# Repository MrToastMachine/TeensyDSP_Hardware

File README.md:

# TeensyDSP Hardware files
Kicad project of files for hardware to use in conjuction with TeensyDSP Firwmware git repo

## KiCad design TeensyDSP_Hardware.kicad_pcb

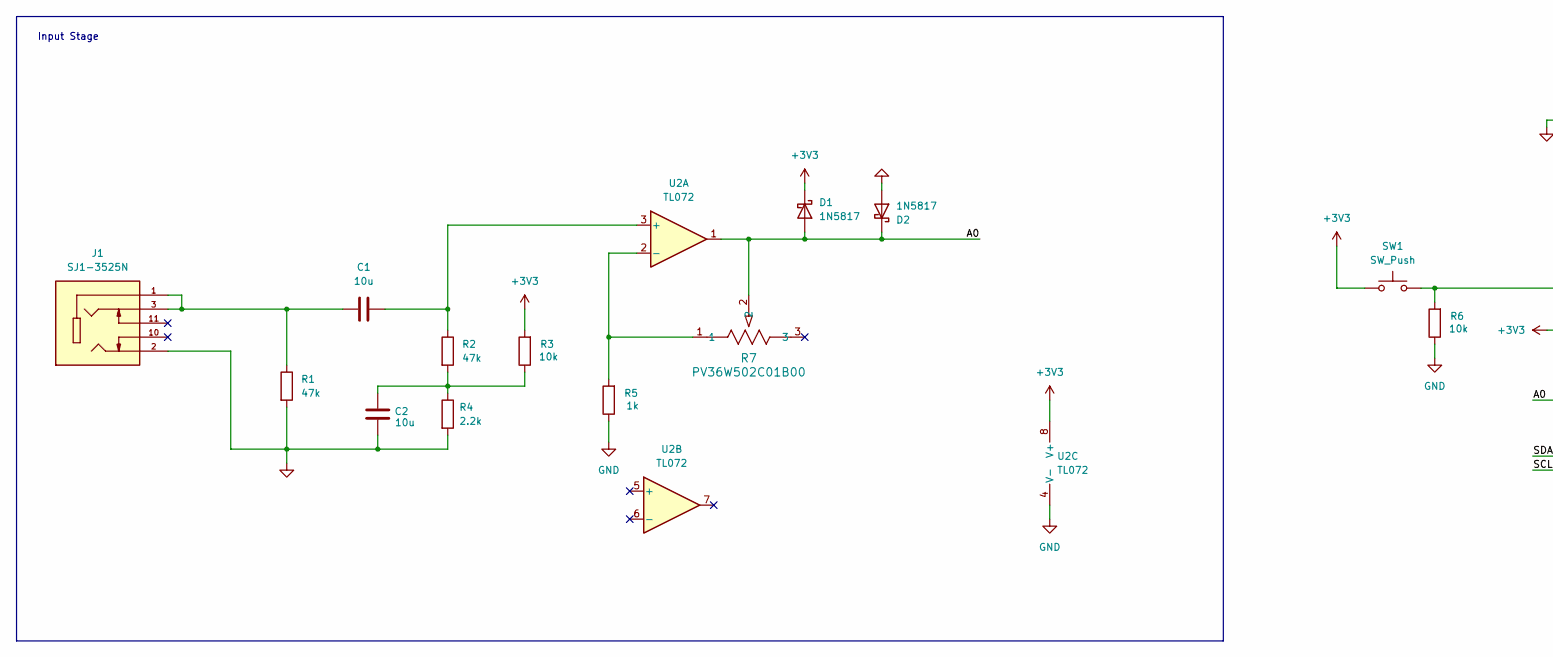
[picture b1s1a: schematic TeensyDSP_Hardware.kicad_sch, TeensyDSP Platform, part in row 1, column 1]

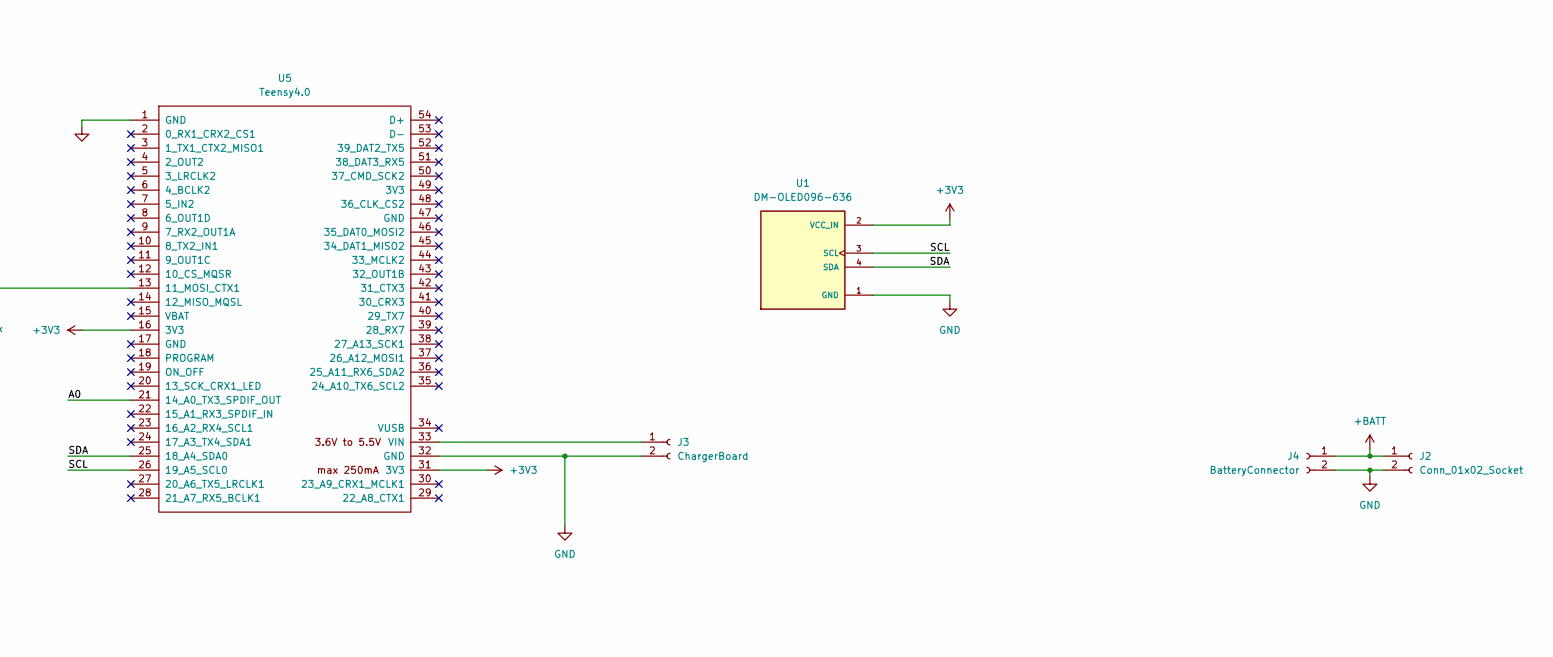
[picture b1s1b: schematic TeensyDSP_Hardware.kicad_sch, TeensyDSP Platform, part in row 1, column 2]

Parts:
C1, C2: 10u; C_Disc_D4.3mm_W1.9mm_P5.00mm
D1, D2: 1N5817; D_DO-41_SOD81_P10.16mm_Horizontal
J1: SJ1-3525N; CUI_SJ1-3525N; PARTREV 1.05
J2: Conn_01x02_Socket; JST_PH_B2B-PH-K_1x02_P2.00mm_Vertical
J3: ChargerBoard; PinHeader_1x02_P2.54mm_Vertical
J4: BatteryConnector; PinHeader_1x02_P2.54mm_Vertical
R1, R2: 47k; R_Axial_DIN0207_L6.3mm_D2.5mm_P7.62mm_Horizontal
R3: 10k; R_Axial_DIN0207_L6.3mm_D2.5mm_P7.62mm_Horizontal
R4: 2.2k; R_Axial_DIN0207_L6.3mm_D2.5mm_P7.62mm_Horizontal
R5: 1k; R_Axial_DIN0207_L6.3mm_D2.5mm_P7.62mm_Horizontal
R6: 10k; R_0603_1608Metric
R7: PV36W502C01B00; POT_PV36W_BRN
SW1: SW_Push; SW_SPST_B3U-3000P
U1: DM-OLED096-636; LED_SCREEN096; PARTREV 2018-09-10
U2: TL072; DIP-8_W7.62mm
U5: Teensy4.0; Teensy40

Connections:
+3V3: D1.1 (K), R3.2, SW1.1, U1.2 (VCC_IN), U2.8 (V+), U5.16 (3V3), U5.31 (3V3)
+BATT: J2.1, J4.1
/A0: D1.2 (A), D2.1 (K), R7.2, U2.1, U5.21 (14_A0_TX3_SPDIF_OUT)
/SCL: U1.3 (SCL), U5.26 (19_A5_SCL0)
/SDA: U1.4 (SDA), U5.25 (18_A4_SDA0)
GND: C2.1, D2.2 (A), J1.2, J2.2, J3.2, J4.2, R1.2, R4.2, R5.1, R6.1, U1.1 (GND), U2.4 (V-), U5.1 (GND), U5.32 (GND)
unnamed: C1.1, J1.1, J1.3, R1.1
unnamed: C2.2, R2.2, R3.1, R4.1
unnamed: J3.1, U5.33 (VIN)
unnamed: C1.2, R2.1, U2.3 (+)
unnamed: R5.2, R7.1, U2.2 (-)
unnamed: R6.2, SW1.2, U5.13 (11_MOSI_CTX1)

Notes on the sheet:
Input Stage

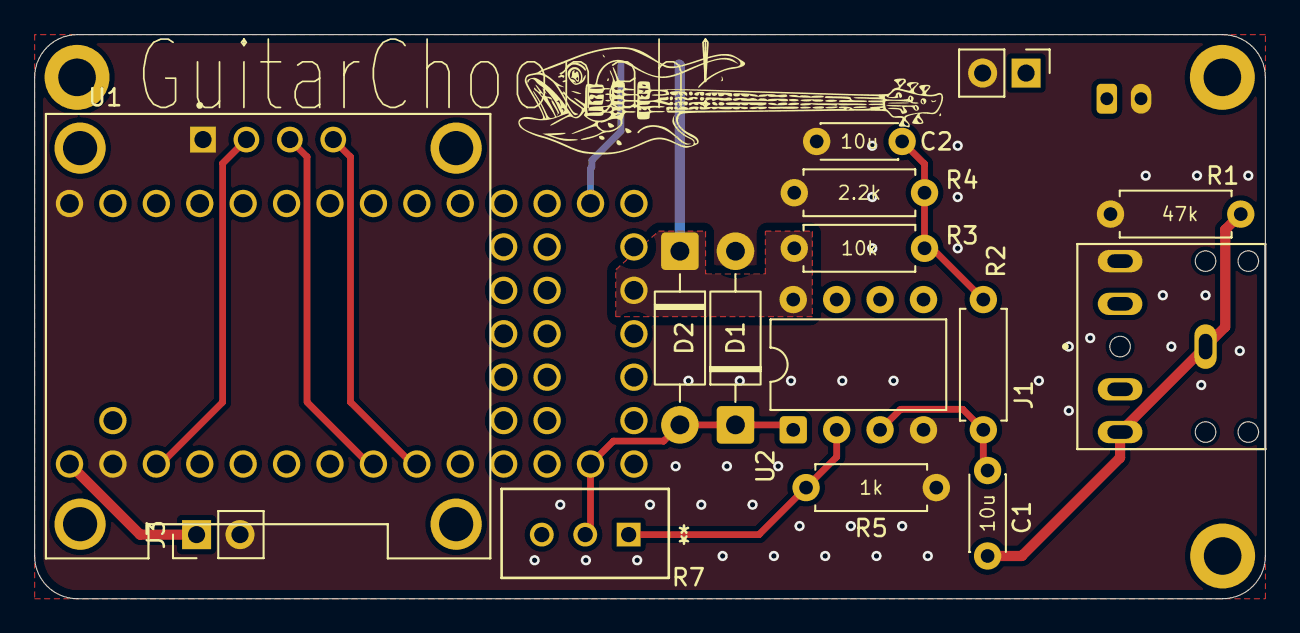
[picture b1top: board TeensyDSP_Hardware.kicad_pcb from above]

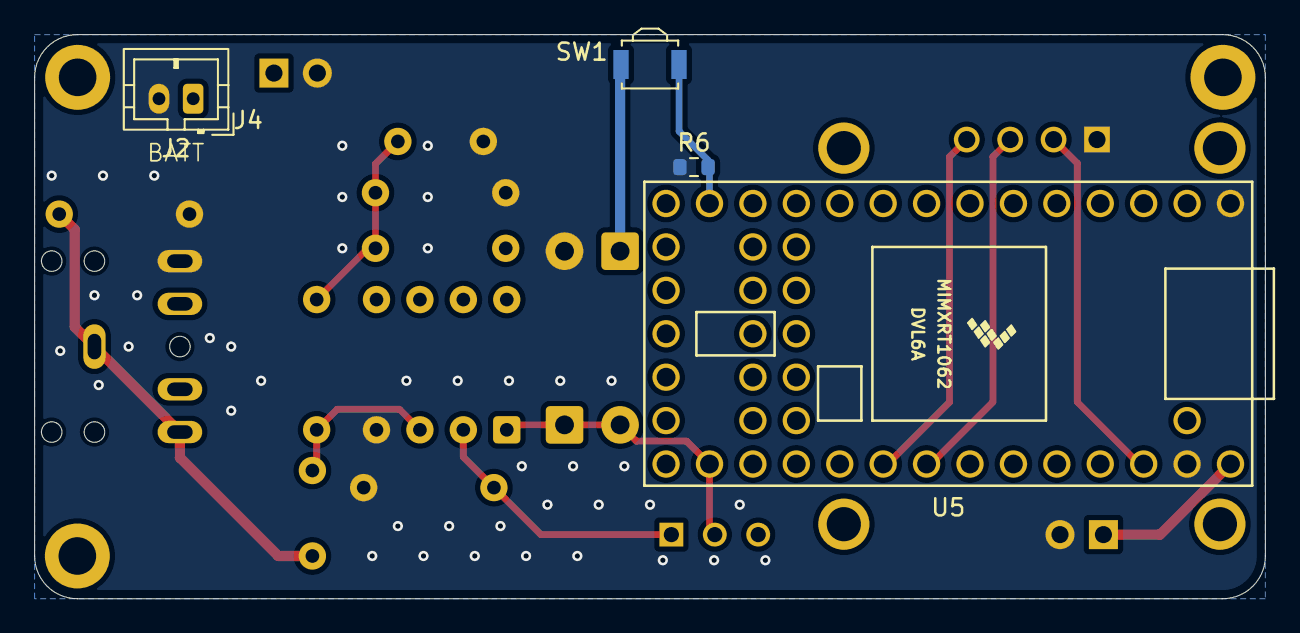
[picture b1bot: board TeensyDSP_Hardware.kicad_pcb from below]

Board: 4 copper layers, 72.0 x 33.0 mm, 19 parts (4 on the bottom side), 12 nets.

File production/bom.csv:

Designator,Footprint,Quantity,Value,LCSC Part #
"C1, C2",C_Disc_D4.3mm_W1.9mm_P5.00mm,2,10u,
"D1, D2",D_DO-41_SOD81_P10.16mm_Horizontal,2,1N5817,
J1,CUI_SJ1-3525N,1,SJ1-3525N,
J2,JST_PH_B2B-PH-K_1x02_P2.00mm_Vertical,1,Conn_01x02_Socket,
J3,PinHeader_1x02_P2.54mm_Vertical,1,ChargerBoard,
J4,PinHeader_1x02_P2.54mm_Vertical,1,BatteryConnector,
"R1, R2",R_Axial_DIN0207_L6.3mm_D2.5mm_P7.62mm_Horizontal,2,47k,
R3,R_Axial_DIN0207_L6.3mm_D2.5mm_P7.62mm_Horizontal,1,10k,
R4,R_Axial_DIN0207_L6.3mm_D2.5mm_P7.62mm_Horizontal,1,2.2k,
R5,R_Axial_DIN0207_L6.3mm_D2.5mm_P7.62mm_Horizontal,1,1k,
R6,0603,1,10k,
R7,POT_PV36W_BRN,1,PV36W502C01B00,
SW1,SW_SPST_B3U-3000P,1,SW_Push,
U1,LED_SCREEN096,1,DM-OLED096-636,
U2,DIP-8_W7.62mm,1,TL072,
U5,Teensy40,1,Teensy4.0,

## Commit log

2026-01-26 Added README
2026-02-19 final commit before change to single ended
2026-05-09 First layout attempt - large footprint
2026-05-18 move toward guitar tuner
2026-05-25 Ordered Guitar Tuner
